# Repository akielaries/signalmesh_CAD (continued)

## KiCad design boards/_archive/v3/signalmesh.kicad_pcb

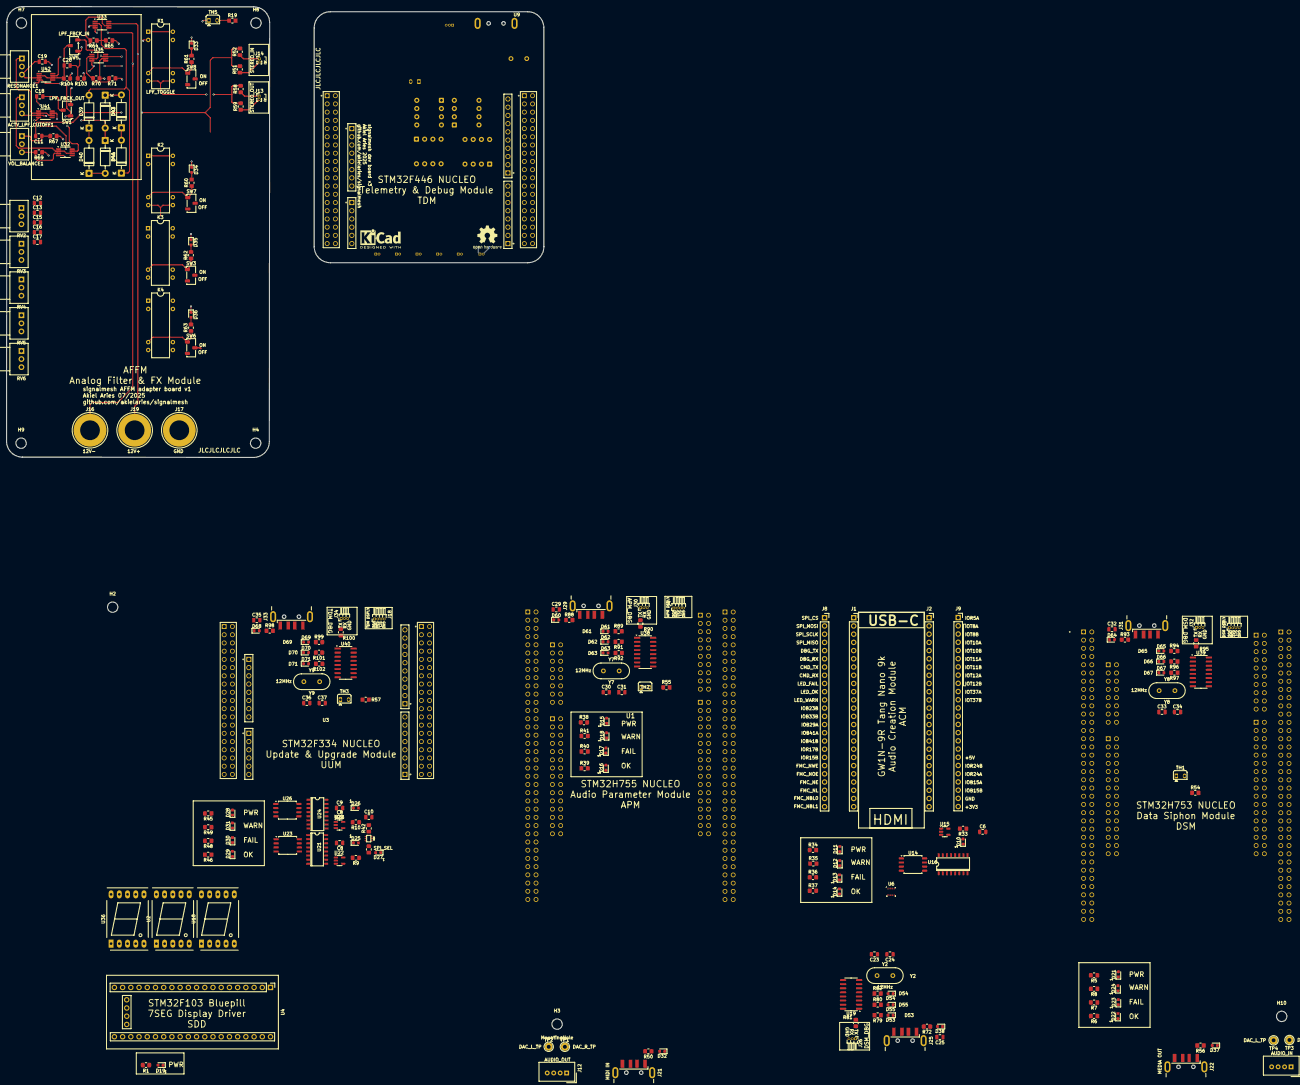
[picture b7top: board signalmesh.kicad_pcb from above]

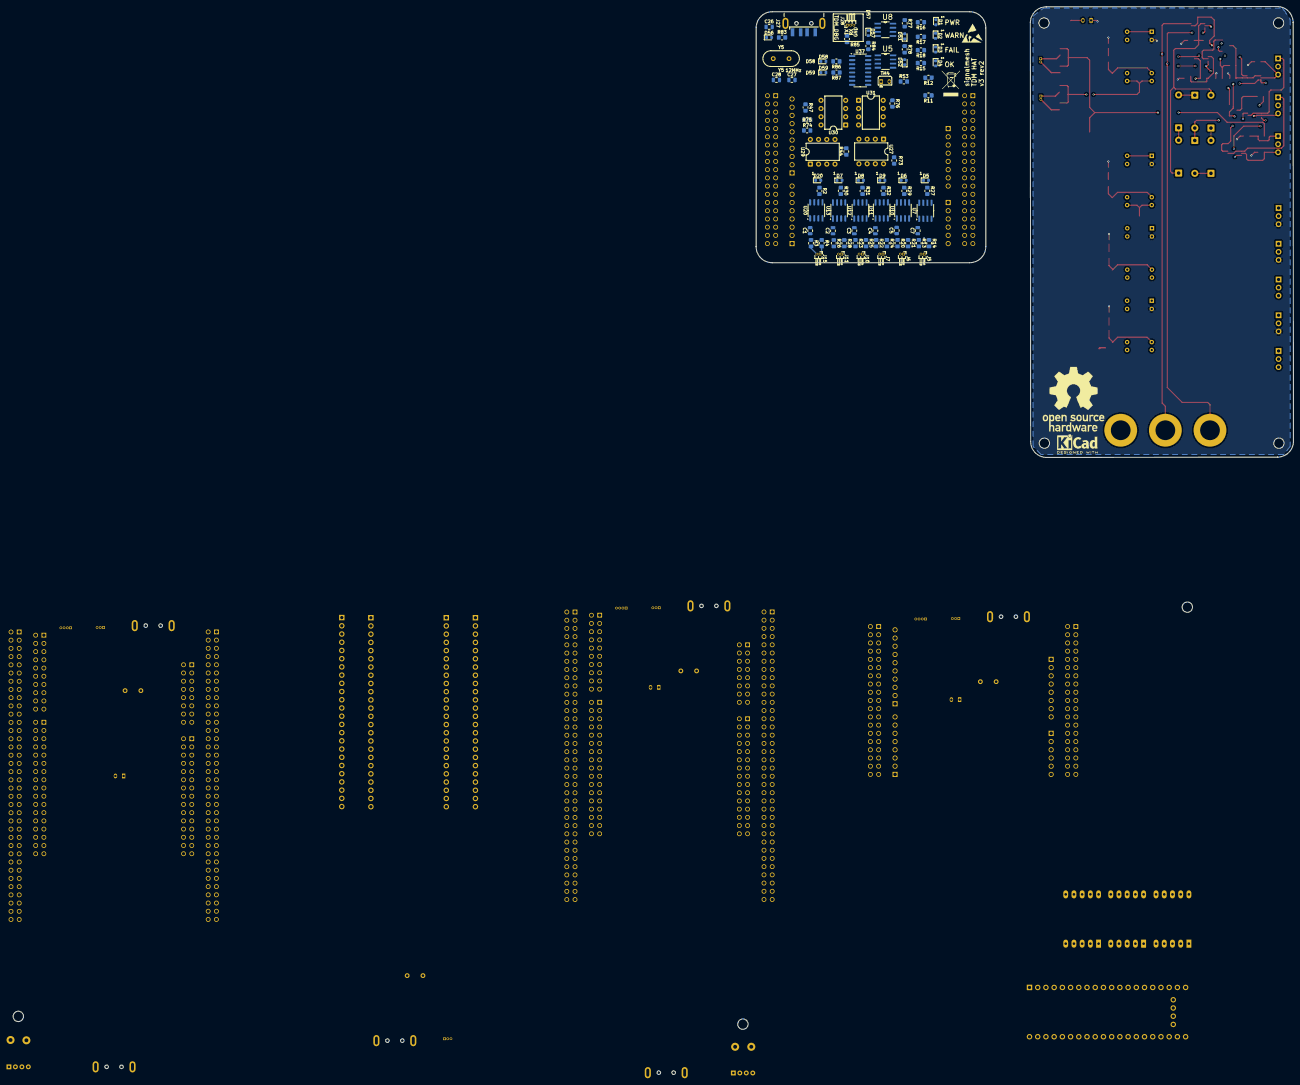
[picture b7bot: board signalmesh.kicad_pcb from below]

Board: 4 copper layers, 166.1 x 139.4 mm, 318 parts (88 on the bottom side), 290 nets.

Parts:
ACTV_LPF_CUTOFF1: 100k; Potentiometer_Alps_RK09Y11_Single_Horizontal
C1, C2, C3, C4, C5, C7, C10, C12, C13, C15, C16, C17: 0.1uf; C_0805_2012Metric
C6, C8, C9: 10uf; C_0805_2012Metric
C11, C20: 1uf; C_0805_2012Metric
C18, C19: 10nf; C_0805_2012Metric
C23, C24, C25, C26, C27, C28, C29, C30, C31, C32, C33, C34, C35, C36, C37: 22pf; C_0805_2012Metric
D1, D12, D16, D22, D29: LED_OK; LED_0603_1608Metric
D2, D13, D17, D23, D30: LED_FAIL; LED_0603_1608Metric
D3, D14, D18, D24, D31: LED_WARN; LED_0603_1608Metric
D4, D5, D6, D7, D8, D9, D10, D11, D15, D19, D20, D21, D25, D26, D28, D32, D37, D38, D51, D52, D53, D56, D57, D60, D61, D64, D65, D68, D69: LED_PWR; LED_0603_1608Metric
D27: SPI_SEL; LED_0603_1608Metric
D33: LPF_ON; LED_0603_1608Metric
D34: HPF_ON; LED_0603_1608Metric
D35: BPF_ON; LED_0603_1608Metric
D36: BSF_ON; LED_0603_1608Metric
D39, D40, D41, D42, D43, D44: 1N4001; D_DO-41_SOD81_P10.16mm_Horizontal
D54, D59, D63, D67, D71: RXD; LED_0603_1608Metric
D55, D58, D62, D66, D70: TXD; LED_0603_1608Metric
H2, H3, H4, H5, H6, H7, H8, H9, H10: MountingHole; MountingHole_3.2mm_M3
J1, J2, J8, J9: FPGA I/O; PinSocket_1x24_P2.54mm_Vertical
J3, J4, J18: LCD_display; PinHeader_1x04_P1.00mm_Horizontal
J5, J6, J7, J10, J11, J15: INA219_CONFIG; PinHeader_1x02_P1.00mm_Horizontal
J12: AUDIO_OUT; NS-Tech_Grove_1x04_P2mm_Vertical
J13: STEREO_OUT; PinHeader_1x02_P1.00mm_Vertical
J14: STEREO_IN; PinHeader_1x02_P1.00mm_Vertical
J16: 12V-; Banana_Jack_1Pin
J17: GND; Banana_Jack_1Pin
J19: 12V+; Banana_Jack_1Pin
J20: AUDIO_IN; NS-Tech_Grove_1x04_P2mm_Vertical
J21, J22, J25, J27, J29, J31, J33: USB_A; USB_A_CNCTech_1001-011-01101_Horizontal
J26, J28, J30, J32, J34: UART_DEBUG; PinHeader_1x03_P1.00mm_Horizontal
K1: LPF_TOGGLE; Relay_StandexMeder_DIP_LowProfile
K2, K3, K4: DIPxx-1Axx-11x; Relay_StandexMeder_DIP_LowProfile
KiCAD_logo: KiCad-Logo2_5mm_SilkScreen
KiCAD_logo#2: KiCad-Logo2_5mm_SilkScreen
OSHW: OSHW-Logo_19x20mm_SilkScreen
R1, R2, R5, R6, R7, R8, R9, R10, R15, R16, R17, R18, R27, R29, R30, R31, R32, R33, R34, R35, R36, R37, R38, R39, R40, R41, R43, R45, R46, R48, R49, R50, R56, R60, R61, R62, R63, R72, R77, R78, R79, R80, R82, R83, R84, R86, R87, R88, R89, R91, R92, R93, R94, R96, R97, R98, R99, R101, R102: 300; R_0805_2012Metric_Pad1.20x1.40mm_HandSolder
R3, R4, R13, R14, R19, R20, R21, R22, R23, R24, R25, R26, R28, R53, R54, R55, R57, R64, R70, R73, R74, R75, R76: 10k; R_0805_2012Metric_Pad1.20x1.40mm_HandSolder
R11, R12: 4.7k; R_0805_2012Metric_Pad1.20x1.40mm_HandSolder
R42: 100; R_0805_2012Metric_Pad1.20x1.40mm_HandSolder
R44, R47: 120; R_0805_2012Metric_Pad1.20x1.40mm_HandSolder
R51, R52: 10K; R_0805_2012Metric_Pad1.20x1.40mm_HandSolder
R58, R59: 1K; R_0805_2012Metric_Pad1.20x1.40mm_HandSolder
R65, R71: 6k8; R_0805_2012Metric_Pad1.20x1.40mm_HandSolder
R67, R103: 200k; R_0805_2012Metric_Pad1.20x1.40mm_HandSolder
R69: 33k; R_0805_2012Metric_Pad1.20x1.40mm_HandSolder
R81, R85, R90, R95, R100: 1k5; R_0805_2012Metric_Pad1.20x1.40mm_HandSolder
R104: 100K; R_0805_2012Metric_Pad1.20x1.40mm_HandSolder
RESONANCE1: 100k; Potentiometer_Alps_RK09Y11_Single_Horizontal
RV2, RV3, RV4, RV5, RV6: 100k; Potentiometer_Alps_RK09Y11_Single_Horizontal
SW1: LPF_FBCK_OUT; Nidec_Copal_CAS-120A
SW3: BPF_TOGGLE; Nidec_Copal_CAS-120A
SW5: LPF_FBCK_IN; Nidec_Copal_CAS-120A
SW6: BSF_TOGGLE; Nidec_Copal_CAS-120A
SW7: HPF_TOGGLE; Nidec_Copal_CAS-120A
SW8: LPF_TOGGLE; Nidec_Copal_CAS-120A
TH1, TH2, TH3, TH4, TH5: 10k; Heraeus_TO-92-2
TP1, TP3: DAC_R_TP; TestPoint_THTPad_D2.5mm_Drill1.2mm
TP2, TP4: DAC_L_TP; TestPoint_THTPad_D2.5mm_Drill1.2mm
U1, U17: NUCLEO-H753ZI; MODULE_NUCLEO-H753ZI
U2, U18, U36: SM420561N; 7SegmentLED_LTS6760_LTS6780
U3: NUCLEO-F303RE; ST_NUCLEO-F303RE
U4: YAAJ_BluePill_Part_Like; YAAJ_WeAct_BlackPill_SWD_2
U5, U8: 24LC256-I_SN; SOIC127P600X175-8N
U6: BME280; Bosch_LGA-8_2.5x2.5mm_P0.65mm_ClockwisePinNumbering
U7, U10, U11, U12, U13, U20: INA219AxD; SOIC-8_3.9x4.9mm_P1.27mm
U9: NUCLEO-F446RE; MODULE_NUCLEO-F446RE
U14, U23, U26: W25Q128JVS; SOIC-8_5.3x5.3mm_P1.27mm
U15, U22, U25: AP2112K-3.3; SOT-23-5
U16, U21, U24: 74HC4050D; SO16
U19, U37, U38, U39, U40: CH340G; SOIC-16_3.9x9.9mm_P1.27mm
U27, U29, U30, U31: MCP2551-I-P; DIP-8_W7.62mm
U28: 74LVC1G3157; SC70-6
U32, U33, U35, U41, U42: OPA196xDGK; VSSOP-8_3x3mm_P0.65mm
VOL_BALANCE1: 100k; Potentiometer_Alps_RK09Y11_Single_Horizontal
Y2, Y5, Y7, Y8, Y9: 12MHz; Crystal_HC49-4H_Vertical

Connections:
3V3_ACM: J2.24, J9.24, U14.3 (~WP/IO_{2}), U14.7 (~HOLD/~RESET/IO_{3}), U16.1 (VCC)
5V_7SDD: R1.2, U4.18 (5V), U20.8 (IN+)
5V_TDM: C1.2, C2.2, C3.2, C4.2, C5.2, C7.2, U7.5 (VS), U7.8 (IN+), U10.5 (VS), U11.5 (VS), U12.5 (VS), U13.5 (VS), U20.5 (VS)
/ACM/ACM_LED_FAIL: J1.9, J8.9, R37.2
/ACM/ACM_LED_OK: J1.10, J8.10, R35.2
/ACM/ACM_LED_WARN: J1.11, J8.11, R36.2
/ACM/ACM_SPI_CS: J1.1, J8.1, U16.3 (1A)
/ACM/ACM_SPI_MISO: J1.4, J8.4, U16.9 (4A)
/ACM/ACM_SPI_MOSI: J1.2, J8.2, U16.7 (3A)
/ACM/ACM_SPI_SCLK: J1.3, J8.3, U16.5 (2A)
/ACM_CMD_RX: J1.7, J8.7, U1.CN11_2 (PC11)
/ACM_CMD_TX: J1.8, J8.8, U1.CN11_1 (PC10)
/ACM_DBG_RX: J1.6, J8.6, J26.2, R82.1, U19.3 (RXD)
/ACM_DBG_TX: J1.5, J8.5, R80.1, R81.2, U19.2 (TXD)
/AFFM/AFFM_filters/BPF_OUT: K3.7, K3.8
/AFFM/AFFM_filters/BPF_TOGGLE: K3.6, R62.1, SW3.1 (C)
/AFFM/AFFM_filters/BSF_OUT: K4.7, K4.8
/AFFM/AFFM_filters/BSF_TOGGLE: K4.6, R63.1, SW6.1 (C)
/AFFM/AFFM_filters/HPF_OUT: K2.7, K2.8
/AFFM/AFFM_filters/HPF_TOGGLE: K2.6, R60.1, SW7.1 (C)
/AFFM/AFFM_filters/LPF_IN: C20.2, K1.1, K1.14, R103.2
/AFFM/AFFM_filters/LPF_OUT: K1.7, K1.8, R58.2, R59.2
/AFFM/AFFM_filters/LPF_TOGGLE: K1.6, R61.1, SW8.1 (C)
/AFFM/AFFM_filters/LPFs/12V+: J19.1, U32.7 (V+), U33.7 (V+), U35.7 (V+), U41.7 (V+), U42.7 (V+)
/AFFM/AFFM_filters/LPFs/12V-: J16.1, U32.4 (V-), U33.4 (V-), U35.4 (V-), U41.4 (V-), U42.4 (V-)
/AFFM/AFFM_filters/LPFs/CFBACK_OUT: SW5.1 (C), U33.3 (+)
/AFFM/AFFM_filters/LPFs/Fback_in: C20.1, R104.2, SW5.2 (B), U42.2 (-), U42.6
/AFFM/AFFM_filters/LPFs/RFBACK_OUT: SW5.3 (A), U35.3 (+)
/AFFM/AFFM_filters/MONO_IN: C11.2, R51.2, R52.2
/APM/7SDD_CMD_RX: U1.CN11_63 (PG9), U4.6 (PA9)
/APM/7SDD_CMD_TX: U1.CN12_61 (PG14), U4.7 (PA10)
/APM/APM_I2C1_SCL: J4.3, U1.CN11_51 (PF1)
/APM/APM_I2C1_SDA: J4.2, U1.CN11_53 (PF0)
/APM/APM_LED_FAIL: R41.2, U1.CN12_34 (PC4)
/APM/APM_LED_OK: R39.2, U1.CN12_4 (PC6)
/APM/APM_LED_WARN: R40.2, U1.CN12_6 (PC5)
/APM/APM_USB_D+: J21.3 (D+), U1.CN12_14 (PA11)
/APM/APM_USB_D-: J21.2 (D-), U1.CN12_12 (PA12)
/APM_CAN_RD: U1.CN12_3 (PB8), U29.1 (TXD)
/APM_CAN_TD: U1.CN12_5 (PB9), U29.4 (RXD)
/APM_DAC_OUT_L: J12.2, J14.2, R51.1, TP1.1, U1.CN12_11 (PA5)
/APM_DAC_OUT_R: J12.3, J14.1, R52.1, TP2.1, U1.CN11_32 (PA4)
/APM_DBG_RX: J30.2, R92.1, U1.CN11_4 (PD2), U38.3 (RXD)
/APM_DBG_TX: R90.2, R91.1, U1.CN11_3 (PC12), U38.2 (TXD)
/CAN+: R44.1, R47.2, U27.7 (CAN+), U29.7 (CAN+), U30.7 (CAN+), U31.7 (CAN+)
/CAN-: R44.2, R47.1, U27.6 (CAN-), U29.6 (CAN-), U30.6 (CAN-), U31.6 (CAN-)
/DSM/DSM_I2C1_SCL: J3.3, U17.CN11_51 (PF1)
/DSM/DSM_I2C1_SDA: J3.2, U17.CN11_53 (PF0)
/DSM/DSM_LED_FAIL: R8.2, U17.CN12_34 (PC4)
/DSM/DSM_LED_OK: R6.2, U17.CN12_4 (PC6)
/DSM/DSM_LED_WARN: R7.2, U17.CN12_6 (PC5)
/DSM/DSM_USB_D+: J22.3 (D+), U17.CN12_14 (PA11)
/DSM/DSM_USB_D-: J22.2 (D-), U17.CN12_12 (PA12)
/DSM_CAN_RD: U17.CN12_3 (PB8), U30.1 (TXD)
/DSM_CAN_TD: U17.CN12_5 (PB9), U30.4 (RXD)
/DSM_DAC_IN_L: J13.1, J20.3, R58.1, TP4.1, U17.CN12_11 (PA5)
/DSM_DAC_IN_R: J13.2, J20.2, R59.1, TP3.1, U17.CN11_32 (PA4)
/DSM_DBG_RX: J32.2, R97.1, U17.CN11_4 (PD2), U39.3 (RXD)
/DSM_DBG_TX: R95.2, R96.1, U17.CN11_3 (PC12), U39.2 (TXD)
/FMC_CLK: J1.18, J8.18, U17.CN11_40 (PD3)
/FMC_D0: J2.1, J9.1, U17.CN12_46 (PD14)
/FMC_D1: J2.2, J9.2, U17.CN12_48 (PD15)
/FMC_D2: J2.3, J9.3, U17.CN11_57 (PD0)
/FMC_D3: J2.4, J9.4, U17.CN11_55 (PD1)
/FMC_D4: J2.5, J9.5, U17.CN12_44 (PE7)
/FMC_D5: J2.6, J9.6, U17.CN12_40 (PE8)
/FMC_D6: J2.7, J9.7, U17.CN12_52 (PE9)
/FMC_D7: J2.8, J9.8, U17.CN12_47 (PE10)
/FMC_D8: J2.9, J9.9, U17.CN12_56 (PE11)
/FMC_D9: J2.10, J9.10, U17.CN12_49 (PE12)
/FMC_D10: J2.11, J9.11, U17.CN12_55 (PE13)
/FMC_D11: J2.12, J9.12, U17.CN12_51 (PE14)
/FMC_D12: J2.13, J9.13, U17.CN12_53 (PE15)
/FMC_D13: J2.14, J9.14, U17.CN12_10 (PD8)
/FMC_D14: J2.15, J9.15, U17.CN11_69 (PD9)
/FMC_D15: J2.16, J9.16, U17.CN12_65 (PD10)
/FMC_NBL0: J1.23, J8.23, U17.CN12_64 (PE0)
/FMC_NBL1: J1.24, J8.24, U17.CN11_61 (PE1)
/FMC_NE: J1.21, J8.21, U17.CN12_19 (PC7)
/FMC_NL: J1.22, J8.22, U17.CN11_21 (PB7)
/FMC_NOE: J1.20, J8.20, U17.CN11_39 (PD4)
/FMC_NWE: J1.19, J8.19, U17.CN11_41 (PD5)
/IRQ0: U1.CN11_62 (PE6), U17.CN11_47 (PE3)
/ISR0: U1.CN11_47 (PE3), U17.CN11_62 (PE6)
/TDM/7SDD_VDD: R2.2, U20.7 (IN-)
/TDM/ACM_VDD: R29.2, U10.7 (IN-)
/TDM/APM_VDD: R30.2, U13.7 (IN-)
/TDM/DSM_VDD: R32.2, U11.7 (IN-)
/TDM/TDM_I2C1_SCL: J18.3, R11.1, U5.6 (SCL), U6.4 (SCK), U7.4 (SCL), U8.6 (SCL), U9.CN10_3 (PB8), U10.4 (SCL), U11.4 (SCL), U12.4 (SCL), U13.4 (SCL), U20.4 (SCL)
/TDM/TDM_I2C1_SDA: J18.2, R12.1, U5.5 (SDA), U6.5 (SDO), U7.3 (SDA), U8.5 (SDA), U9.CN10_5 (PB9), U10.3 (SDA), U11.3 (SDA), U12.3 (SDA), U13.3 (SDA), U20.3 (SDA)
/TDM/TDM_LED_FAIL: R18.2, U9.CN10_6 (PC5)
/TDM/TDM_LED_OK: R16.2, U9.CN10_11 (PA5)
/TDM/TDM_LED_WARN: R17.2, U9.CN10_34 (PC4)
/TDM/UUM_VDD: R31.2, U12.7 (IN-)
/TDM_CAN_RD: U9.CN10_14 (PA11), U31.1 (TXD)
/TDM_CAN_TD: U9.CN10_12 (PA12), U31.4 (RXD)
/TDM_DBG_RX: J28.2, R87.1, U9.CN10_37 (PA3), U37.3 (RXD)
/TDM_DBG_TX: R85.2, R86.1, U9.CN10_35 (PA2), U37.2 (TXD)
/USB_debug_ACM/D+: J25.3 (D+), U19.5 (UD+)
/USB_debug_ACM/D-: J25.2 (D-), U19.6 (UD-)
/USB_debug_ACM/DBG_TX: J26.1, R81.1
/USB_debug_APM/D+: J29.3 (D+), U38.5 (UD+)
/USB_debug_APM/D-: J29.2 (D-), U38.6 (UD-)
/USB_debug_APM/DBG_TX: J30.1, R90.1
/USB_debug_DSM/D+: J31.3 (D+), U39.5 (UD+)
/USB_debug_DSM/D-: J31.2 (D-), U39.6 (UD-)
/USB_debug_DSM/DBG_TX: J32.1, R95.1
/USB_debug_TDM/D+: J27.3 (D+), U37.5 (UD+)
/USB_debug_TDM/D-: J27.2 (D-), U37.6 (UD-)
/USB_debug_TDM/DBG_TX: J28.1, R85.1
/USB_debug_UUM/D+: J33.3 (D+), U40.5 (UD+)
/USB_debug_UUM/D-: J33.2 (D-), U40.6 (UD-)
/USB_debug_UUM/DBG_TX: J34.1, R100.1
/UUM/UUM_LED_FAIL: R49.2, U3.CN7_38 (PC0)
/UUM/UUM_LED_OK: R46.2, U3.CN7_35 (PC2)
/UUM/UUM_LED_WARN: R48.2, U3.CN7_36 (PC1)
/UUM/UUM_SPI1_CS: U3.CN10_23 (PA8), U21.3 (1A)
/UUM/UUM_SPI1_MISO: U3.CN10_13 (PA6), U28.6
/UUM/UUM_SPI1_MOSI: U3.CN10_15 (PA7), U21.7 (3A), U24.7 (3A)
/UUM/UUM_SPI1_SCLK: U3.CN10_11 (PA5), U21.5 (2A), U24.5 (2A)
/UUM/UUM_SPI2_CS: U3.CN10_21 (PA9), U24.3 (1A)
/UUM/UUM_SPI_SEL: R43.1, U3.CN7_25 (PC14), U28.4
/UUM/UUM_spiflash/UUM_SPI1_MISO_A: U21.9 (4A), U28.3
/UUM/UUM_spiflash/UUM_SPI1_MISO_B: U24.9 (4A), U28.1
/UUM_CAN_RD: U3.CN10_3 (PB8), U27.1 (TXD)
/UUM_CAN_TD: U3.CN10_5 (PB9), U27.4 (RXD)
/UUM_DBG_RX: J34.2, R102.1, U3.CN10_37 (PA3), U40.3 (RXD)
/UUM_DBG_TX: R100.2, R101.1, U3.CN10_35 (PA2), U40.2 (TXD)
ACM_VDD: C25.2, J2.18, J9.18, J25.1 (VBUS), R34.2, R72.2, R79.2, U15.1 (VIN), U15.3 (EN), U19.16 (VCC)
APM_VDD: C29.2, J4.1, J21.1 (VBUS), J29.1 (VBUS), R38.2, R50.2, R88.2, R89.2, SW3.2 (B), SW6.2 (B), SW7.2 (B), SW8.2 (B), U1.CN11_18 (5V), U29.3 (VDD), U38.16 (VCC)
DSM_VDD: C32.2, J3.1, J22.1 (VBUS), J31.1 (VBUS), R5.2, R56.2, R93.2, R94.2, U17.CN11_18 (5V), U30.3 (VDD), U39.16 (VCC)
GND: C1.1, C2.1, C3.1, C4.1, C5.1, C6.2, C7.1, C8.2, C9.2, C10.2, C15.1, C17.1, C19.2, C23.2, C24.2, C25.1, C26.1, C27.2, C28.2, C29.1, C30.2, C31.2, C32.1, C33.2, C34.2, C35.1, C36.2, C37.2, D1.1 (K), D2.1 (K), D3.1 (K), D4.1 (K), D5.1 (K), D6.1 (K), D7.1 (K), D8.1 (K), D9.1 (K), D10.1 (K), D11.1 (K), D12.1 (K), D13.1 (K), D14.1 (K), D15.1 (K), D16.1 (K), D17.1 (K), D18.1 (K), D19.1 (K), D20.1 (K), D21.1 (K), D22.1 (K), D23.1 (K), D24.1 (K), D25.1 (K), D26.1 (K), D27.1 (K), D28.1 (K), D29.1 (K), D30.1 (K), D31.1 (K), D32.1 (K), D33.1 (K), D34.1 (K), D35.1 (K), D36.1 (K), D37.1 (K), D38.1 (K), D51.1 (K), D52.1 (K), D53.1 (K), D54.1 (K), D55.1 (K), D56.1 (K), D57.1 (K), D58.1 (K), D59.1 (K), D60.1 (K), D61.1 (K), D62.1 (K), D63.1 (K), D64.1 (K), D65.1 (K), D66.1 (K), D67.1 (K), D68.1 (K), D69.1 (K), D70.1 (K), D71.1 (K), J2.23, J3.4, J4.4, J9.23, J12.4, J18.4, J20.4, J21.4 (GND), J22.4 (GND), J25.4 (GND), J26.3, J27.4 (GND), J28.3, J29.4 (GND), J30.3, J31.4 (GND), J32.3, J33.4 (GND), J34.3, K1.2, K2.2, K3.2, K4.2, R3.1, R4.1, R13.1, R14.1, R20.1, R21.1, R22.1, R23.1, R24.1, R25.1, R26.1, R28.1, R65.1, R67.1, R69.1, R71.1, R73.2, R74.2, R75.2, R76.2, R103.1, R104.1, RV2.3, RV3.3, RV5.3, TH1.1, TH2.1, TH3.1, TH4.1, TH5.1, U1.CN11_8 (GND_CN11), U1.CN11_19 (GND_CN11), U1.CN11_20 (GND_CN11), U1.CN11_22 (GND_CN11), U1.CN11_49 (GND_CN11), U1.CN11_60 (GND_CN11), U1.CN11_71 (GND_CN11), U1.CN11_72 (GND_CN11), U2.3 (CC), U2.8 (CC), U3.CN10_9 (GND_S2), U3.CN10_20 (GND_S2), U4.39 (GND), U5.1 (A0), U5.2 (A1), U5.3 (A2), U5.4 (VSS), U6.1 (GND), U6.7 (GND), U7.6 (GND), U8.1 (A0), U8.3 (A2), U8.4 (VSS), U9.CN10_9 (CN10_GND), U9.CN10_20 (CN10_GND), U10.6 (GND), U11.6 (GND), U12.6 (GND), U13.6 (GND), U14.4 (GND), U15.2 (GND), U16.8 (GND), U16.11 (5A), U16.14 (6A), U17.CN11_8 (GND_CN11), U17.CN11_19 (GND_CN11), U17.CN11_20 (GND_CN11), U17.CN11_22 (GND_CN11), U17.CN11_49 (GND_CN11), U17.CN11_60 (GND_CN11), U17.CN11_71 (GND_CN11), U17.CN11_72 (GND_CN11), U18.3 (CC), U18.8 (CC), U19.1 (GND), U20.6 (GND), U21.8 (GND), U21.11 (5A), U21.14 (6A), U22.2 (GND), U23.4 (GND), U24.8 (GND), U24.11 (5A), U24.14 (6A), U25.2 (GND), U26.4 (GND), U27.2 (VSS), U28.2 (GND), U29.2 (VSS), U30.2 (VSS), U31.2 (VSS), U36.3 (CC), U36.8 (CC), U37.1 (GND), U38.1 (GND), U39.1 (GND), U40.1 (GND)
unnamed: C10.1, R42.2
unnamed: C11.1, R67.2, VOL_BALANCE1.1
unnamed: C12.1, RV2.1
unnamed: C13.1, RV3.1
unnamed: C15.2, RV4.3
unnamed: C16.1, RV5.1
unnamed: C16.2, RV6.1
unnamed: C17.2, RV6.3
unnamed: D1.2 (A), R16.1
unnamed: D2.2 (A), R17.1
unnamed: D3.2 (A), R18.1
unnamed: D4.2 (A), R15.1
unnamed: D5.2 (A), R27.1
unnamed: D6.2 (A), R29.1
unnamed: D7.2 (A), R30.1
unnamed: D8.2 (A), R31.1
unnamed: D9.2 (A), R32.1
unnamed: D10.2 (A), R33.2
unnamed: D11.2 (A), R34.1
unnamed: D12.2 (A), R35.1
unnamed: D13.2 (A), R36.1
unnamed: D14.2 (A), R37.1
unnamed: D15.2 (A), R38.1
unnamed: D16.2 (A), R39.1
unnamed: D17.2 (A), R40.1
unnamed: D18.2 (A), R41.1
unnamed: D19.2 (A), R1.1
unnamed: D20.2 (A), R2.1
unnamed: D21.2 (A), R5.1
unnamed: D22.2 (A), R6.1
unnamed: D23.2 (A), R7.1
unnamed: D24.2 (A), R8.1
unnamed: D25.2 (A), R9.2
unnamed: D26.2 (A), R10.2
unnamed: D27.2 (A), R43.2
unnamed: D28.2 (A), R45.1
unnamed: D29.2 (A), R46.1
unnamed: D30.2 (A), R48.1
unnamed: D31.2 (A), R49.1
unnamed: D32.2 (A), R50.1
unnamed: D33.2 (A), R61.2
unnamed: D34.2 (A), R60.2
unnamed: D35.2 (A), R62.2
unnamed: D36.2 (A), R63.2
unnamed: D37.2 (A), R56.1
unnamed: D38.2 (A), R72.1
unnamed: D39.2 (A), D44.1 (K), R64.1, R65.2, U33.2 (-)
unnamed: D39.1 (K), D40.2 (A)
unnamed: D40.1 (K), D41.2 (A)
unnamed: D41.1 (K), D42.2 (A), R64.2, SW1.1 (C), U33.6
unnamed: D42.1 (K), D43.2 (A)
unnamed: D43.1 (K), D44.2 (A)
unnamed: D51.2 (A), R77.2
unnamed: D52.2 (A), R78.2
unnamed: D53.2 (A), R79.1
unnamed: D54.2 (A), R82.2
unnamed: D55.2 (A), R80.2
unnamed: D56.2 (A), R83.1
unnamed: D57.2 (A), R84.1
unnamed: D58.2 (A), R86.2
unnamed: D59.2 (A), R87.2
unnamed: D60.2 (A), R88.1
unnamed: D61.2 (A), R89.1
unnamed: D62.2 (A), R91.2
unnamed: D63.2 (A), R92.2
unnamed: D64.2 (A), R93.1
unnamed: D65.2 (A), R94.1
unnamed: D66.2 (A), R96.2
unnamed: D67.2 (A), R97.2
unnamed: D68.2 (A), R98.1
unnamed: D69.2 (A), R99.1
unnamed: D70.2 (A), R101.2
unnamed: D71.2 (A), R102.2
unnamed: J5.1, R14.2, U7.1 (A1)
unnamed: J5.2, R13.2, U7.2 (A0)
unnamed: J6.1, R21.2, U10.1 (A1)
unnamed: J6.2, R20.2, U10.2 (A0)
unnamed: J7.1, R24.2, U11.1 (A1)
unnamed: J7.2, R22.2, U11.2 (A0)
unnamed: J10.1, R25.2, U12.1 (A1)
unnamed: J10.2, R23.2, U12.2 (A0)
unnamed: J11.1, R28.2, U13.1 (A1)
unnamed: J11.2, R26.2, U13.2 (A0)
unnamed: J15.1, R4.2, U20.1 (A1)
unnamed: J15.2, R3.2, U20.2 (A0)
unnamed: K2.1, K2.14
unnamed: K3.1, K3.14
unnamed: K4.1, K4.14
unnamed: R19.1, TH5.2
unnamed: RV3.2, RV4.1
unnamed: R70.1, SW1.3 (A), U35.6
unnamed: C18.2, SW1.2 (B)
unnamed: U2.7 (A), U4.28 (PA3)
unnamed: U2.6 (B), U4.27 (PA2)
unnamed: U2.4 (C), U4.26 (PA1)
unnamed: U2.2 (D), U4.25 (PA0)
unnamed: U2.5 (DP), U4.16 (PB8)
unnamed: U2.1 (E), U4.24 (PC15)
unnamed: U2.9 (F), U4.23 (PC14)
unnamed: U2.10 (G), U4.17 (PB9)
unnamed: R57.1, TH3.2, U9.CN7_32 (PA4)
unnamed: R55.1, TH2.2, U9.CN7_34 (PB0)
unnamed: R54.1, TH1.2, U9.CN7_38 (PC0/PB8)
unnamed: R53.1, TH4.2, U9.CN7_36 (PC1/PB9)
unnamed: U14.6 (CLK), U16.4 (2Y)
unnamed: U14.5 (DI/IO_{0}), U16.6 (3Y)
unnamed: U14.2 (DO/IO_{1}), U16.10 (4Y)
unnamed: C6.1, R33.1, U14.8 (VCC), U15.5 (VOUT)
unnamed: U14.1 (~CS), U16.2 (1Y)
unnamed: U4.36 (PB11), U18.7 (A)
unnamed: U4.35 (PB10), U18.6 (B)
unnamed: U4.34 (PB1), U18.4 (C)
unnamed: U4.33 (PB0), U18.2 (D)
unnamed: U4.29 (PA4), U18.5 (DP)
unnamed: U4.32 (PA7), U18.1 (E)
unnamed: U4.31 (PA6), U18.9 (F)
unnamed: U4.30 (PA5), U18.10 (G)
unnamed: C24.1, U19.7 (XI), Y2.1
unnamed: C23.1, U19.8 (XO), Y2.2
unnamed: U21.2 (1Y), U23.1 (~CS)
unnamed: U21.4 (2Y), U23.6 (CLK)
unnamed: U21.6 (3Y), U23.5 (DI/IO_{0})
unnamed: U21.10 (4Y), U23.2 (DO/IO_{1})
unnamed: C8.1, R9.1, U22.5 (VOUT), U23.8 (VCC)
unnamed: U24.2 (1Y), U26.1 (~CS)
unnamed: U24.4 (2Y), U26.6 (CLK)
unnamed: U24.6 (3Y), U26.5 (DI/IO_{0})
unnamed: U24.10 (4Y), U26.2 (DO/IO_{1})
unnamed: C9.1, R10.1, U25.5 (VOUT), U26.8 (VCC)
unnamed: R73.1, U27.8 (Rs)
unnamed: R74.1, U29.8 (Rs)
unnamed: R75.1, U30.8 (Rs)
unnamed: R76.1, U31.8 (Rs)
unnamed: R69.2, U32.3 (+), VOL_BALANCE1.3
unnamed: ACTV_LPF_CUTOFF1.1, U32.2 (-), U32.6
unnamed: R70.2, R71.2, U35.2 (-)
unnamed: U4.15 (PB7), U36.7 (A)
unnamed: U4.14 (PB6), U36.6 (B)
unnamed: U4.13 (PB5), U36.4 (C)
unnamed: U4.12 (PB4), U36.2 (D)
unnamed: U4.8 (PA11), U36.5 (DP)
unnamed: U4.11 (PB3), U36.1 (E)
unnamed: U4.10 (PA15), U36.9 (F)
unnamed: U4.9 (PA12), U36.10 (G)
unnamed: C27.1, U37.7 (XI), Y5.1
unnamed: C28.1, U37.8 (XO), Y5.2
unnamed: C30.1, U38.7 (XI), Y7.1
unnamed: C31.1, U38.8 (XO), Y7.2
unnamed: C33.1, U39.7 (XI), Y8.1
unnamed: C34.1, U39.8 (XO), Y8.2
unnamed: C36.1, U40.7 (XI), Y9.1
unnamed: C37.1, U40.8 (XO), Y9.2
unnamed: ACTV_LPF_CUTOFF1.3, C18.1, U41.3 (+)
unnamed: RESONANCE1.1, U41.2 (-), U41.6
unnamed: C19.1, RESONANCE1.3, U42.3 (+)
TDM_VDD: C26.2, J18.1, J27.1 (VBUS), R11.2, R12.2, R15.2, R19.2, R27.2, R53.2, R54.2, R55.2, R57.2, R77.1, R78.1, R83.2, R84.2, U5.8 (VCC), U6.8 (VDD), U7.7 (IN-), U8.8 (VCC), U9.CN10_8 (U5V), U31.3 (VDD), U37.16 (VCC)
UUM_3v3: R42.1, U3.CN7_16 (+3V3_S1), U21.1 (VCC), U23.3 (~WP/IO_{2}), U23.7 (~HOLD/~RESET/IO_{3}), U24.1 (VCC), U26.3 (~WP/IO_{2}), U26.7 (~HOLD/~RESET/IO_{3}), U28.5 (VCC)
UUM_VDD: C35.2, J33.1 (VBUS), R45.2, R98.2, R99.2, U3.CN7_18 (+5V_S1), U22.1 (VIN), U22.3 (EN), U25.1 (VIN), U25.3 (EN), U27.3 (VDD), U40.16 (VCC)

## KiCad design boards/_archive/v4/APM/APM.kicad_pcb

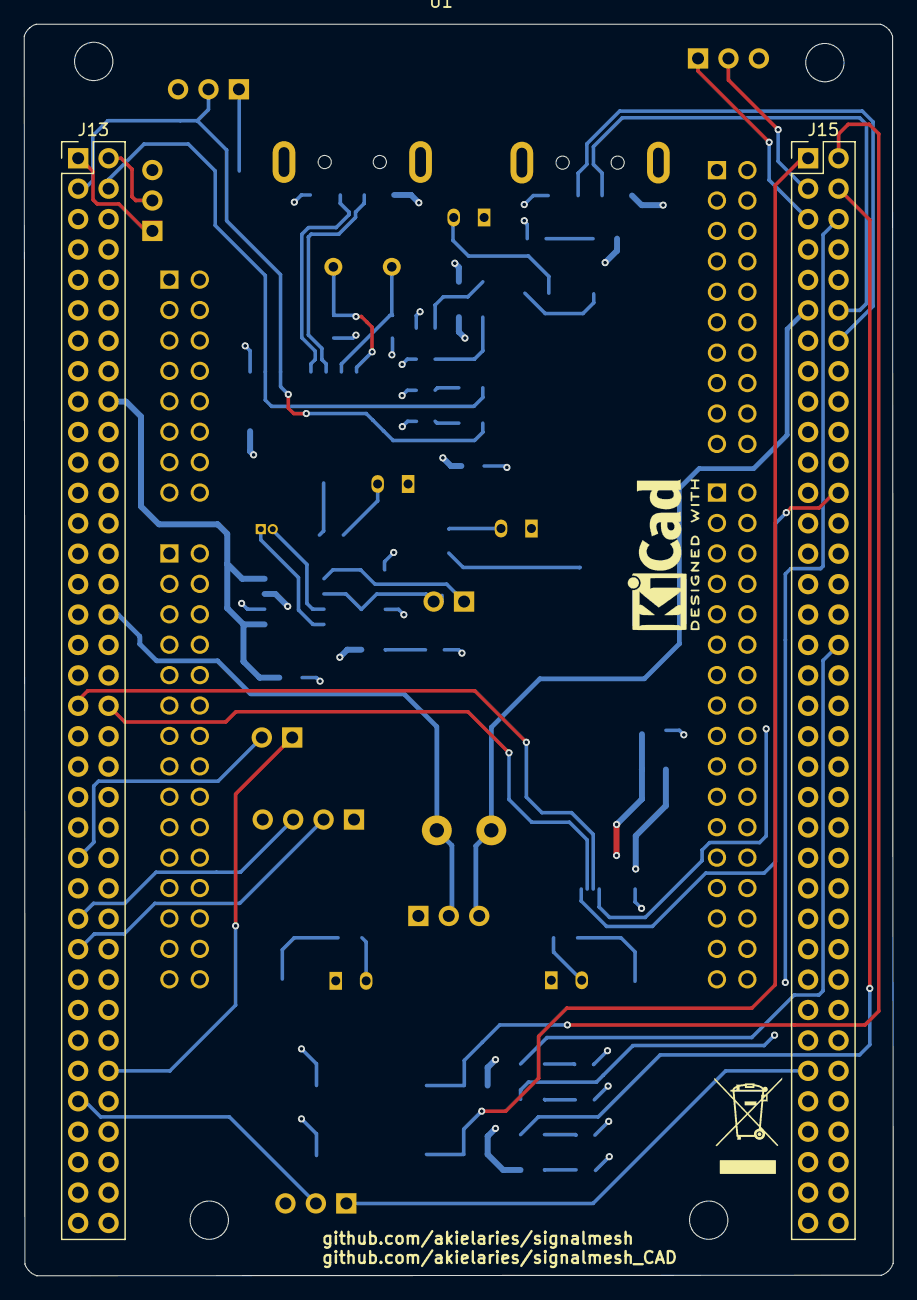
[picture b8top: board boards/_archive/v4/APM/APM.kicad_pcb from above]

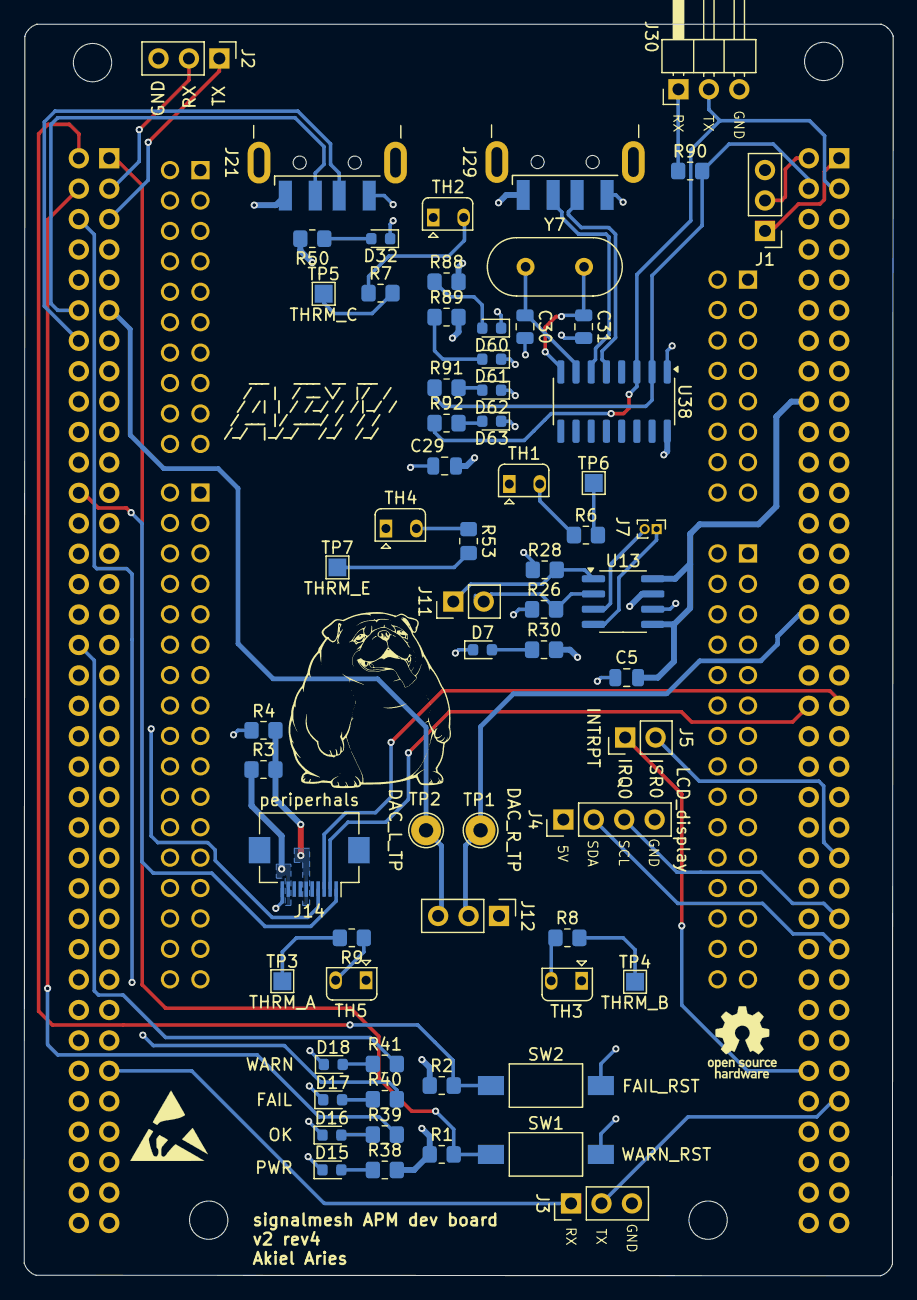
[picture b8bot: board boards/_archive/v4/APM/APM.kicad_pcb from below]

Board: 4 copper layers, 72.5 x 104.5 mm, 68 parts (65 on the bottom side), 58 nets.

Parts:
C5: 0.1uf; C_0805_2012Metric
C29, C30, C31: 22pf; C_0805_2012Metric
D7, D32, D60, D61: LED_PWR; LED_0603_1608Metric
D15: PWR; LED_0603_1608Metric
D16: OK; LED_0603_1608Metric
D17: FAIL; LED_0603_1608Metric
D18: WARN; LED_0603_1608Metric
D62: TXD; LED_0603_1608Metric
D63: RXD; LED_0603_1608Metric
J1: ACM_CTRL; PinHeader_1x03_P2.54mm_Vertical
J2: CAN; PinHeader_1x03_P2.54mm_Vertical
J3: 7SDD_CTRL; PinHeader_1x03_P2.54mm_Vertical
J4: LCD_display; PinHeader_1x04_P2.54mm_Vertical
J5: INTRPT; PinHeader_1x02_P2.54mm_Vertical
J7: TDM_PMS_I2C; PinHeader_1x02_P1.00mm_Vertical
J11: INA219_CONFIG; PinHeader_1x02_P2.54mm_Vertical
J12: AUDIO_OUT; PinHeader_1x03_P2.54mm_Vertical
J13, J15: Conn_02x36_Odd_Even; PinHeader_2x36_P2.54mm_Vertical
J14: periperhals; Hirose_FH12-10S-0.5SH_1x10-1MP_P0.50mm_Horizontal
J21, J29: USB_A; USB_A_CNCTech_1001-011-01101_Horizontal
J30: UART_DEBUG; PinHeader_1x03_P2.54mm_Horizontal
R1, R2, R30, R38, R39, R40, R41, R50, R88, R89, R91, R92: 300; R_0805_2012Metric_Pad1.20x1.40mm_HandSolder
R3, R6, R7, R8, R9, R26, R28, R53: 10k; R_0805_2012Metric_Pad1.20x1.40mm_HandSolder
R4: 20k; R_0805_2012Metric_Pad1.20x1.40mm_HandSolder
R90: 1k5; R_0805_2012Metric_Pad1.20x1.40mm_HandSolder
SW1: WARN_RST; SW_SPST_FSMSM
SW2: FAIL_RST; SW_SPST_FSMSM
TH1, TH2, TH3, TH4, TH5: 10k; Heraeus_TO-92-2
TP1: DAC_R_TP; TestPoint_THTPad_D2.5mm_Drill1.2mm
TP2: DAC_L_TP; TestPoint_THTPad_D2.5mm_Drill1.2mm
TP3: THRM_A; TestPoint_Pad_1.5x1.5mm
TP4: THRM_B; TestPoint_Pad_1.5x1.5mm
TP5: THRM_C; TestPoint_Pad_1.5x1.5mm
TP6: THRM_D; TestPoint_Pad_1.5x1.5mm
TP7: THRM_E; TestPoint_Pad_1.5x1.5mm
U1: NUCLEO-H753ZI; ST_Morpho_and_Zio_Connectors_144_STLink
U13: INA219AxD; SOIC-8_3.9x4.9mm_P1.27mm
U38: CH340G; SOIC-16_3.9x9.9mm_P1.27mm
Y7: 12MHz; Crystal_HC49-4H_Vertical

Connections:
5V_APM: C29.2, J4.1, J14.9, J21.1 (VBUS), J29.1 (VBUS), R1.1, R2.1, R3.1, R30.2, R38.2, R50.2, R88.2, R89.2, U13.7 (IN-), U38.16 (VCC)
5V_APM_MCU: C5.2, J13.18, U13.5 (VS), U13.8 (IN+)
/3V3_APM: J14.6, R3.2, R4.1
/7SDD_CMD_RX: J3.2, J13.63
/7SDD_CMD_TX: J3.1, J15.61
/APM_CAN_RD: J2.2, J15.3
/APM_CAN_TD: J2.1, J15.5
/APM_CMD_RX: J1.2, J13.2
/APM_CMD_TX: J1.1, J13.1
/APM_DAC_L: J12.3, J15.11, TP2.1
/APM_DAC_R: J12.2, J13.32, TP1.1
/APM_DBG_RX: J13.4, R90.2, R91.1, U38.2 (TXD)
/APM_DBG_TX: J13.3, J30.2, R92.1, U38.3 (RXD)
/APM_FAIL_RST: J15.2, R2.2, SW2.1
/APM_I2C1_SCL: J4.3, J13.51
/APM_I2C1_SDA: J4.2, J13.53
/APM_IRQ0: J5.1, J13.62
/APM_ISR0: J5.2, J13.47
/APM_LED_FAIL: J15.34, R41.2
/APM_LED_OK: J15.4, R39.2
/APM_LED_WARN: J15.6, R40.2
/APM_USB_D+: J15.14, J21.3 (D+)
/APM_USB_D-: J15.12, J21.2 (D-)
/APM_WARN_RST: J15.1, R1.2, SW1.1
/POT_1: J14.1, J15.24
/POT_2: J13.38, J14.2
/POT_3: J13.37, J14.3
/POT_4: J14.4, J15.37
/TDM_SCL: J7.1, U13.4 (SCL)
/TDM_SDA: J7.2, U13.3 (SDA)
/THRM_A: R9.2, TP3.1
/THRM_B: R8.2, TP4.1
/THRM_C: R7.2, TP5.1
/THRM_D: R6.2, TP6.1
/THRM_E: R53.2, TP7.1
/USB_debug_APM/APM_DBG_TX: J30.1, R90.1
/USB_debug_APM/D+: J29.3 (D+), U38.5 (UD+)
/USB_debug_APM/D-: J29.2 (D-), U38.6 (UD-)
GND: C5.1, C29.1, C30.2, C31.2, D7.1 (K), D15.1 (K), D16.1 (K), D17.1 (K), D18.1 (K), D32.1 (K), D60.1 (K), D61.1 (K), D62.1 (K), D63.1 (K), J1.3, J2.3, J3.3, J4.4, J13.8, J14.10, J21.4 (GND), J29.4 (GND), J30.3, R4.2, R26.1, R28.1, SW1.2, SW2.2, TH1.1, TH2.1, TH3.1, TH4.1, TH5.1, U13.6 (GND), U38.1 (GND)
unnamed: D7.2 (A), R30.1
unnamed: D15.2 (A), R38.1
unnamed: D16.2 (A), R39.1
unnamed: D17.2 (A), R40.1
unnamed: D18.2 (A), R41.1
unnamed: D32.2 (A), R50.1
unnamed: D60.2 (A), R88.1
unnamed: D61.2 (A), R89.1
unnamed: D62.2 (A), R91.2
unnamed: D63.2 (A), R92.2
unnamed: J11.1, R28.2, U13.1 (A1)
unnamed: J11.2, R26.2, U13.2 (A0)
unnamed: R6.1, TH1.2
unnamed: R7.1, TH2.2
unnamed: R8.1, TH3.2
unnamed: R9.1, TH5.2
unnamed: R53.1, TH4.2
unnamed: C30.1, U38.7 (XI), Y7.1
unnamed: C31.1, U38.8 (XO), Y7.2
